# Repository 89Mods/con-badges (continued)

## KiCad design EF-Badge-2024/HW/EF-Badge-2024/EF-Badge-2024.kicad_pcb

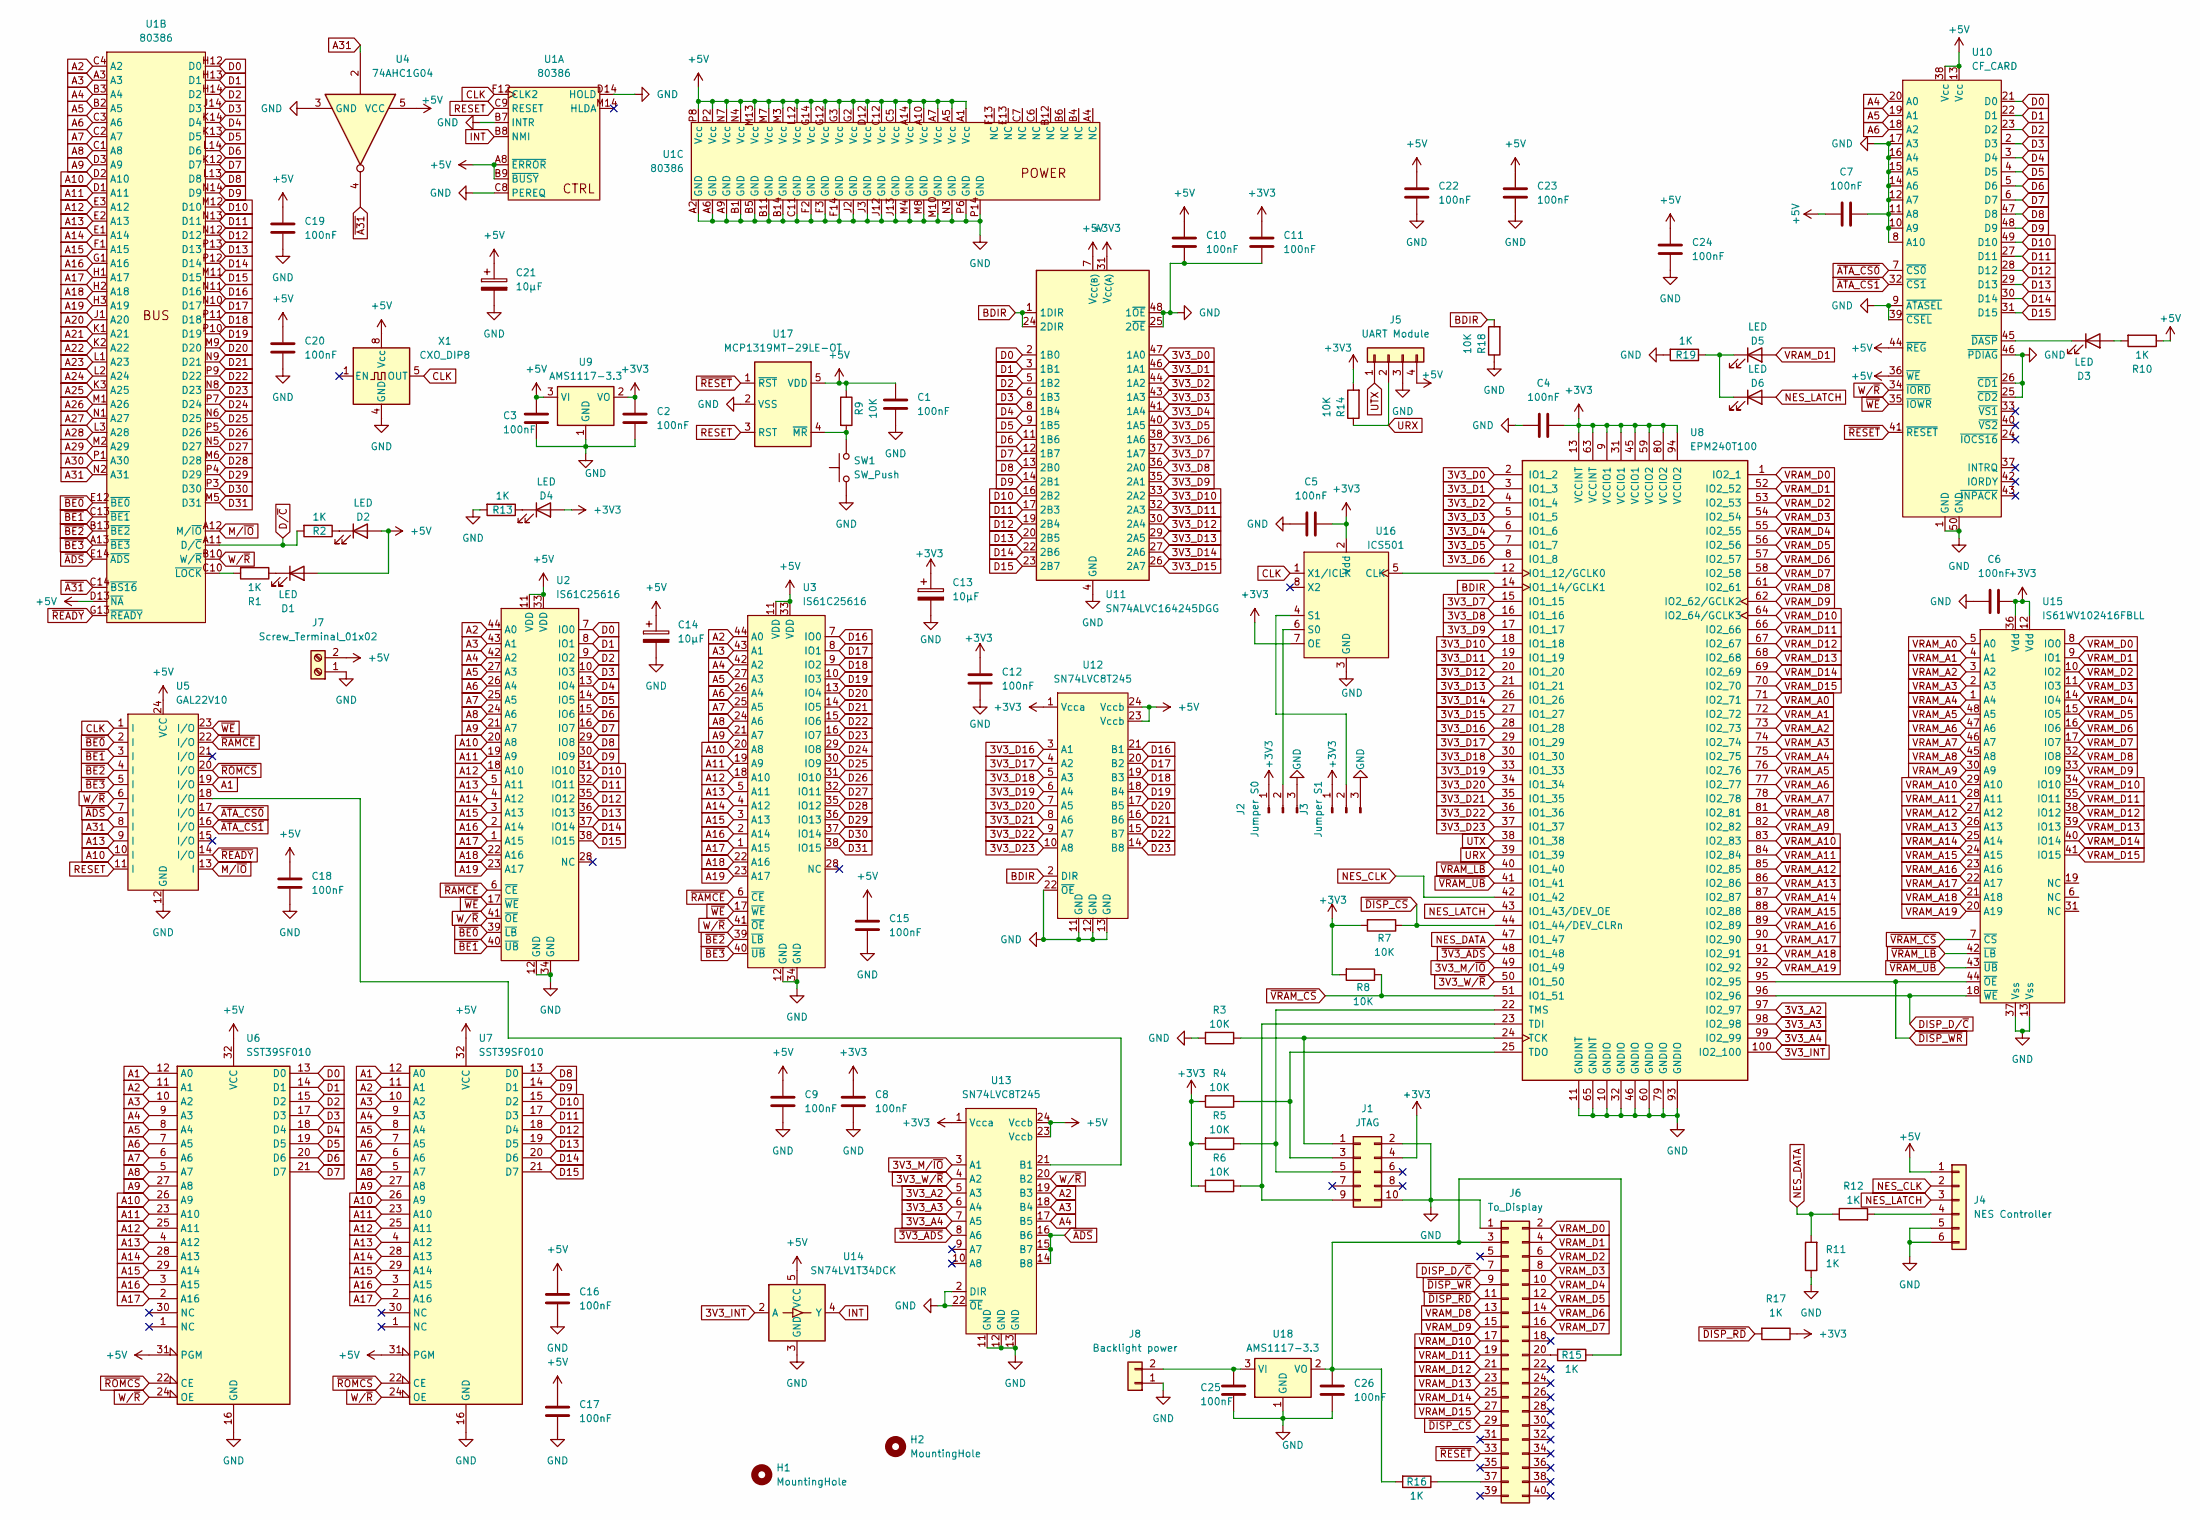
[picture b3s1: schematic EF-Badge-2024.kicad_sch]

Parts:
C1, C2, C3, C4, C5, C6, C7, C8, C9, C10, C11, C12, C15, C16, C17, C18, C19, C20, C22, C23, C24, C25, C26: 100nF; C_0805_2012Metric_Pad1.18x1.45mm_HandSolder
C13, C14, C21: 10µF; CP_Elec_3x5.4
D1, D2, D3, D4, D5, D6: LED; LED_1206_3216Metric_Pad1.42x1.75mm_HandSolder
H1, H2: MountingHole; MountingHole_3.2mm_M3_ISO7380
J1: JTAG; PinHeader_2x05_P2.54mm_Vertical
J2: Jumper S0; PinHeader_1x03_P2.54mm_Vertical
J3: Jumper S1; PinHeader_1x03_P2.54mm_Vertical
J4: NES Controller; PinSocket_1x06_P2.54mm_Vertical
J5: UART Module; PinHeader_1x04_P2.54mm_Vertical
J6: To_Display; PinHeader_2x20_P2.54mm_Vertical
J7: Screw_Terminal_01x02; TerminalBlock_bornier-2_P5.08mm
J8: Backlight power; PinHeader_1x02_P2.54mm_Vertical
R1, R2, R10, R11, R12, R13, R15, R16, R17, R19: 1K; R_1206_3216Metric_Pad1.30x1.75mm_HandSolder
R3, R4, R5, R6, R7, R8, R9, R14, R18: 10K; R_1206_3216Metric_Pad1.30x1.75mm_HandSolder
SW1: SW_Push; SW_PUSH_6mm
U1: 80386; Intel386DX
U2, U3: IS61C25616; TSOP-II-44_10.16x18.41mm_P0.8mm
U4: 74AHC1G04; SOIC-6
U5: GAL22V10; DIP-24_W7.62mm_Socket
U6, U7: SST39SF010; PLCC-32_THT-Socket
U8: EPM240T100; LQFP-100_14x14mm_P0.5mm
U9, U18: AMS1117-3.3; SOT-223-3_TabPin2
U10: CF_CARD; CF-Card_3M_N7E50-E516xx-30_fixed
U11: SN74ALVC164245DGG; TSSOP-48_6.1x12.5mm_P0.5mm
U12, U13: SN74LVC8T245; TSSOP-24_4.4x7.8mm_P0.65mm
U14: SN74LV1T34DCK; SOT-23-5
U15: IS61WV102416FBLL; TSOP-I-48_18.4x12mm_P0.5mm
U16: ICS501; SOIC-8_3.9x4.9mm_P1.27mm
U17: MCP1319MT-29LE-OT; SOT-23-5
X1: CXO_DIP8; Oscillator_DIP-8

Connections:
3V3_A2: U8.97 (IO2_97), U13.5 (A3)
3V3_A3: U8.98 (IO2_98), U13.6 (A4)
3V3_A4: U8.99 (IO2_99), U13.7 (A5)
3V3_D0: U8.2 (IO1_2), U11.47 (1A0)
3V3_D1: U8.3 (IO1_3), U11.46 (1A1)
3V3_D2: U8.4 (IO1_4), U11.44 (1A2)
3V3_D3: U8.5 (IO1_5), U11.43 (1A3)
3V3_D4: U8.6 (IO1_6), U11.41 (1A4)
3V3_D5: U8.7 (IO1_7), U11.40 (1A5)
3V3_D6: U8.8 (IO1_8), U11.38 (1A6)
3V3_D7: U8.15 (IO1_15), U11.37 (1A7)
3V3_D8: U8.16 (IO1_16), U11.36 (2A0)
3V3_D9: U8.17 (IO1_17), U11.35 (2A1)
3V3_D10: U8.18 (IO1_18), U11.33 (2A2)
3V3_D11: U8.19 (IO1_19), U11.32 (2A3)
3V3_D12: U8.20 (IO1_20), U11.30 (2A4)
3V3_D13: U8.21 (IO1_21), U11.29 (2A5)
3V3_D14: U8.26 (IO1_26), U11.27 (2A6)
3V3_D15: U8.27 (IO1_27), U11.26 (2A7)
3V3_D16: U8.28 (IO1_28), U12.3 (A1)
3V3_D17: U8.29 (IO1_29), U12.4 (A2)
3V3_D18: U8.30 (IO1_30), U12.5 (A3)
3V3_D19: U8.33 (IO1_33), U12.6 (A4)
3V3_D20: U8.34 (IO1_34), U12.7 (A5)
3V3_D21: U8.35 (IO1_35), U12.8 (A6)
3V3_D22: U8.36 (IO1_36), U12.9 (A7)
3V3_D23: U8.37 (IO1_37), U12.10 (A8)
3V3_INT: U8.100 (IO2_100), U14.2 (A)
3V3_M/~IO: U8.49 (IO1_49), U13.3 (A1)
3V3_W/~R: U8.50 (IO1_50), U13.4 (A2)
+3V3: C2.1, C4.2, C5.2, C6.2, C8.2, C11.2, C12.2, C13.1, D4.2 (A), J1.4, J2.1, J3.1, R4.2, R5.2, R6.2, R7.2, R8.2, R14.2, R17.1, U8.9 (VCCIO1), U8.13 (VCCINT), U8.31 (VCCIO1), U8.45 (VCCIO1), U8.59 (VCCIO2), U8.63 (VCCINT), U8.80 (VCCIO2), U8.94 (VCCIO2), U9.2 (VO), U11.31 (V_{CC(A)}), U11.42 (V_{CC(A)}), U12.1 (Vcca), U13.1 (Vcca), U15.12 (Vdd), U15.36 (Vdd), U16.2 (Vdd), U16.7 (OE)
+5V: C1.1, C3.1, C7.1, C9.2, C10.2, C14.1, C15.2, C16.2, C17.2, C18.2, C19.2, C20.2, C21.1, C22.2, C23.2, C24.2, D1.2 (A), D2.2 (A), J4.1, J5.4, J7.2, R9.1, R10.1, U1.A1 (Vcc), U1.A5 (Vcc), U1.A7 (Vcc), U1.A8 (~ERROR), U1.A10 (Vcc), U1.A14 (Vcc), U1.B9 (~BUSY), U1.C5 (Vcc), U1.C12 (Vcc), U1.D12 (Vcc), U1.D13 (~NA), U1.G2 (Vcc), U1.G3 (Vcc), U1.G12 (Vcc), U1.G14 (Vcc), U1.L12 (Vcc), U1.M3 (Vcc), U1.M7 (Vcc), U1.M13 (Vcc), U1.N4 (Vcc), U1.N7 (Vcc), U1.P2 (Vcc), U1.P8 (Vcc), U2.11 (VDD), U2.33 (VDD), U3.11 (VDD), U3.33 (VDD), U4.5 (VCC), U5.24 (VCC), U6.31 (PGM), U6.32 (VCC), U7.31 (PGM), U7.32 (VCC), U9.3 (VI), U10.13 (Vcc), U10.36 (~WE), U10.38 (Vcc), U10.44 (~REG), U11.7 (V_{CC(B)}), U11.18 (V_{CC(B)}), U12.23 (Vccb), U12.24 (Vccb), U13.23 (Vccb), U13.24 (Vccb), U14.5 (VCC), U17.5 (VDD), X1.8 (Vcc)
A1: U5.19 (I/O), U6.12 (A0), U7.12 (A0)
A2: U1.C4 (A2), U2.44 (A0), U3.44 (A0), U6.11 (A1), U7.11 (A1), U13.19 (B3)
A3: U1.A3, U2.43 (A1), U3.43 (A1), U6.10 (A2), U7.10 (A2), U13.18 (B4)
A4: U1.B3 (A4), U2.42 (A2), U3.42 (A2), U6.9 (A3), U7.9 (A3), U10.20 (A0), U13.17 (B5)
A5: U1.B2 (A5), U2.27 (A3), U3.27 (A3), U6.8 (A4), U7.8 (A4), U10.19 (A1)
A6: U1.C3 (A6), U2.26 (A4), U3.26 (A4), U6.7 (A5), U7.7 (A5), U10.18 (A2)
A7: U1.C2 (A7), U2.25 (A5), U3.25 (A5), U6.6 (A6), U7.6 (A6)
A8: U1.C1 (A8), U2.24 (A6), U3.24 (A6), U6.5 (A7), U7.5 (A7)
A9: U1.D3 (A9), U2.21 (A7), U3.21 (A7), U6.27 (A8), U7.27 (A8)
A10: U1.D2 (A10), U2.20 (A8), U3.20 (A8), U5.10 (I), U6.26 (A9), U7.26 (A9)
A11: U1.D1 (A11), U2.19 (A9), U3.19 (A9), U6.23 (A10), U7.23 (A10)
A12: U1.E3 (A12), U2.18 (A10), U3.18 (A10), U6.25 (A11), U7.25 (A11)
A13: U1.E2 (A13), U2.5 (A11), U3.5 (A11), U5.9 (I), U6.4 (A12), U7.4 (A12)
A14: U1.E1 (A14), U2.4 (A12), U3.4 (A12), U6.28 (A13), U7.28 (A13)
A15: U1.F1 (A15), U2.3 (A13), U3.3 (A13), U6.29 (A14), U7.29 (A14)
A16: U1.G1 (A16), U2.2 (A14), U3.2 (A14), U6.3 (A15), U7.3 (A15)
A17: U1.H1 (A17), U2.1 (A15), U3.1 (A15), U6.2 (A16), U7.2 (A16)
A18: U1.H2 (A18), U2.22 (A16), U3.22 (A16)
A19: U1.H3 (A19), U2.23 (A17), U3.23 (A17)
A20: U1.J1 (A20)
A21: U1.K1 (A21)
A22: U1.K2 (A22)
A23: U1.L1 (A23)
A24: U1.L2 (A24)
A25: U1.K3 (A25)
A26: U1.M1 (A26)
A27: U1.N1 (A27)
A28: U1.L3 (A28)
A29: U1.M2 (A29)
A30: U1.P1 (A30)
A31: U1.N2 (A31), U4.2, U5.8 (I)
BDIR: R18.2, U8.14 (IO1_14/GCLK1), U11.1 (1DIR), U11.24 (2DIR), U12.2 (DIR)
CLK: U1.F12 (CLK2), U5.1 (I), U16.1 (X1/ICLK), X1.5 (OUT)
D0: U1.H12 (D0), U2.7 (IO0), U6.13 (D0), U10.21 (D0), U11.2 (1B0)
D1: U1.H13 (D1), U2.8 (IO1), U6.14 (D1), U10.22 (D1), U11.3 (1B1)
D2: U1.H14 (D2), U2.9 (IO2), U6.15 (D2), U10.23 (D2), U11.5 (1B2)
D3: U1.J14 (D3), U2.10 (IO3), U6.17 (D3), U10.2 (D3), U11.6 (1B3)
D4: U1.K14 (D4), U2.13 (IO4), U6.18 (D4), U10.3 (D4), U11.8 (1B4)
D5: U1.K13 (D5), U2.14 (IO5), U6.19 (D5), U10.4 (D5), U11.9 (1B5)
D6: U1.L14 (D6), U2.15 (IO6), U6.20 (D6), U10.5 (D6), U11.11 (1B6)
D7: U1.K12 (D7), U2.16 (IO7), U6.21 (D7), U10.6 (D7), U11.12 (1B7)
D8: U1.L13 (D8), U2.29 (IO8), U7.13 (D0), U10.47 (D8), U11.13 (2B0)
D9: U1.N14 (D9), U2.30 (IO9), U7.14 (D1), U10.48 (D9), U11.14 (2B1)
D10: U1.M12 (D10), U2.31 (IO10), U7.15 (D2), U10.49 (D10), U11.16 (2B2)
D11: U1.N13 (D11), U2.32 (IO11), U7.17 (D3), U10.27 (D11), U11.17 (2B3)
D12: U1.N12 (D12), U2.35 (IO12), U7.18 (D4), U10.28 (D12), U11.19 (2B4)
D13: U1.P13 (D13), U2.36 (IO13), U7.19 (D5), U10.29 (D13), U11.20 (2B5)
D14: U1.P12 (D14), U2.37 (IO14), U7.20 (D6), U10.30 (D14), U11.22 (2B6)
D15: U1.M11 (D15), U2.38 (IO15), U7.21 (D7), U10.31 (D15), U11.23 (2B7)
D16: U1.N11 (D16), U3.7 (IO0), U12.21 (B1)
D17: U1.N10 (D17), U3.8 (IO1), U12.20 (B2)
D18: U1.P11 (D18), U3.9 (IO2), U12.19 (B3)
D19: U1.P10 (D19), U3.10 (IO3), U12.18 (B4)
D20: U1.M9 (D20), U3.13 (IO4), U12.17 (B5)
D21: U1.N9 (D21), U3.14 (IO5), U12.16 (B6)
D22: U1.P9 (D22), U3.15 (IO6), U12.15 (B7)
D23: U1.N8 (D23), U3.16 (IO7), U12.14 (B8)
D24: U1.P7 (D24), U3.29 (IO8)
D25: U1.N6 (D25), U3.30 (IO9)
D26: U1.P5 (D26), U3.31 (IO10)
D27: U1.N5 (D27), U3.32 (IO11)
D28: U1.M6 (D28), U3.35 (IO12)
D29: U1.P4 (D29), U3.36 (IO13)
D30: U1.P3 (D30), U3.37 (IO14)
D31: U1.M5 (D31), U3.38 (IO15)
DISP_D/~C: J6.7, U8.96 (IO2_96), U15.18 (~WE)
D/~C: R2.2, U1.A11 (D/~C)
GND: C1.2, C2.2, C3.2, C4.1, C5.1, C6.1, C7.2, C8.1, C9.1, C10.1, C11.1, C12.1, C13.2, C14.2, C15.1, C16.1, C17.1, C18.1, C19.1, C20.1, C21.2, C22.1, C23.1, C24.1, C25.2, C26.2, J1.2, J1.10, J2.3, J3.3, J4.5, J4.6, J5.3, J6.1, J7.1, J8.1, R3.2, R11.1, R13.2, R18.1, R19.2, SW1.1, U1.A2 (GND), U1.A6 (GND), U1.A9 (GND), U1.B1 (GND), U1.B5 (GND), U1.B7 (INTR), U1.B11 (GND), U1.B14 (GND), U1.C8 (PEREQ), U1.C11 (GND), U1.D14 (HOLD), U1.F2 (GND), U1.F3 (GND), U1.F14 (GND), U1.J2 (GND), U1.J3 (GND), U1.J12 (GND), U1.J13 (GND), U1.M4 (GND), U1.M8 (GND), U1.M10 (GND), U1.N3 (GND), U1.P6 (GND), U1.P14 (GND), U2.12 (GND), U2.34 (GND), U3.12 (GND), U3.34 (GND), U4.3 (GND), U5.12 (GND), U6.16 (GND), U7.16 (GND), U8.10 (GNDIO), U8.11 (GNDINT), U8.32 (GNDIO), U8.46 (GNDIO), U8.60 (GNDIO), U8.65 (GNDINT), U8.79 (GNDIO), U8.93 (GNDIO), U9.1 (GND), U10.1 (GND), U10.8 (A10), U10.9 (~ATASEL), U10.10 (A9), U10.11 (A8), U10.12 (A7), U10.14 (A6), U10.15 (A5), U10.16 (A4), U10.17 (A3), U10.25 (~CD2), U10.26 (~CD1), U10.39 (~CSEL), U10.46 (~PDIAG), U10.50 (GND), U11.4 (GND), U11.10 (GND), U11.15 (GND), U11.21 (GND), U11.25 (2~OE), U11.28 (GND), U11.34 (GND), U11.39 (GND), U11.45 (GND), U11.48 (1~OE), U12.11 (GND), U12.12 (GND), U12.13 (GND), U12.22 (~OE), U13.2 (DIR), U13.11 (GND), U13.12 (GND), U13.13 (GND), U13.22 (~OE), U14.3 (GND), U15.13 (Vss), U15.37 (Vss), U16.3 (GND), U17.2 (VSS), U18.1 (GND), X1.4 (GND)
INT: U1.B8 (NMI), U14.4 (Y)
M/~IO: U1.A12 (M/~IO), U5.13 (I)
NES_CLK: J4.2, U8.42 (IO1_42)
NES_DATA: R11.2, R12.1, U8.47 (IO1_47)
NES_LATCH: D6.2 (A), J4.3, U8.43 (IO1_43/DEV_OE)
unnamed: D1.1 (K), R1.1
unnamed: D2.1 (K), R2.1
unnamed: D3.2 (A), R10.2
unnamed: D3.1 (K), U10.45 (~DASP)
unnamed: D4.1 (K), R13.1
unnamed: D5.1 (K), D6.1 (K), R19.1
unnamed: J1.1, R3.1, U8.24 (TCK)
unnamed: J1.3, R4.1, U8.25 (TDO)
unnamed: J1.5, R5.1, U8.22 (TMS)
unnamed: J1.9, R6.1, U8.23 (TDI)
unnamed: J2.2, U16.6 (S0)
unnamed: J3.2, U16.4 (S1)
unnamed: J4.4, R12.2
unnamed: C26.1, J6.3, R15.1, R16.2, U18.2 (VO)
unnamed: J6.20, R15.2
unnamed: J6.37, R16.1
unnamed: C25.1, J8.2, U18.3 (VI)
unnamed: R1.2, U1.C10 (~LOCK)
unnamed: U5.18 (I/O), U13.21 (B1)
unnamed: U8.12 (IO1_12/GCLK0), U16.5 (CLK)
unnamed: R9.2, SW1.2, U17.4 (~MR)
RESET: U1.C9 (RESET), U5.11 (I), U17.3 (RST)
URX: J5.2, R14.1, U8.39 (IO1_39)
UTX: J5.1, U8.38 (IO1_38)
VRAM_A0: U8.71 (IO2_71), U15.5 (A0)
VRAM_A1: U8.72 (IO2_72), U15.4 (A1)
VRAM_A2: U8.73 (IO2_73), U15.3 (A2)
VRAM_A3: U8.74 (IO2_74), U15.2 (A3)
VRAM_A4: U8.75 (IO2_75), U15.1 (A4)
VRAM_A5: U8.76 (IO2_76), U15.48 (A5)
VRAM_A6: U8.77 (IO2_77), U15.47 (A6)
VRAM_A7: U8.78 (IO2_78), U15.46 (A7)
VRAM_A8: U8.81 (IO2_81), U15.45 (A8)
VRAM_A9: U8.82 (IO2_82), U15.30 (A9)
VRAM_A10: U8.83 (IO2_83), U15.29 (A10)
VRAM_A11: U8.84 (IO2_84), U15.28 (A11)
VRAM_A12: U8.85 (IO2_85), U15.27 (A12)
VRAM_A13: U8.86 (IO2_86), U15.26 (A13)
VRAM_A14: U8.87 (IO2_87), U15.25 (A14)
VRAM_A15: U8.88 (IO2_88), U15.24 (A15)
VRAM_A16: U8.89 (IO2_89), U15.23 (A16)
VRAM_A17: U8.90 (IO2_90), U15.22 (A17)
VRAM_A18: U8.91 (IO2_91), U15.21 (A18)
VRAM_A19: U8.92 (IO2_92), U15.20 (A19)
VRAM_D0: J6.2, U8.1 (IO2_1), U15.8 (IO0)
VRAM_D1: D5.2 (A), J6.4, U8.52 (IO2_52), U15.9 (IO1)
VRAM_D2: J6.6, U8.53 (IO2_53), U15.10 (IO2)
VRAM_D3: J6.8, U8.54 (IO2_54), U15.11 (IO3)
VRAM_D4: J6.10, U8.55 (IO2_55), U15.14 (IO4)
VRAM_D5: J6.12, U8.56 (IO2_56), U15.15 (IO5)
VRAM_D6: J6.14, U8.57 (IO2_57), U15.16 (IO6)
VRAM_D7: J6.16, U8.58 (IO2_58), U15.17 (IO7)
VRAM_D8: J6.13, U8.61 (IO2_61), U15.32 (IO8)
VRAM_D9: J6.15, U8.62 (IO2_62/GCLK2), U15.33 (IO9)
VRAM_D10: J6.17, U8.64 (IO2_64/GCLK3), U15.34 (IO10)
VRAM_D11: J6.19, U8.66 (IO2_66), U15.35 (IO11)
VRAM_D12: J6.21, U8.67 (IO2_67), U15.38 (IO12)
VRAM_D13: J6.23, U8.68 (IO2_68), U15.39 (IO13)
VRAM_D14: J6.25, U8.69 (IO2_69), U15.40 (IO14)
VRAM_D15: J6.27, U8.70 (IO2_70), U15.41 (IO15)
W/~R: U1.B10 (W/~R), U2.41 (~OE), U3.41 (~OE), U5.6 (I), U6.24 (OE), U7.24 (OE), U10.34 (~IORD), U13.20 (B2)
~3V3_ADS: U8.48 (IO1_48), U13.8 (A6)
~A31: U1.C14 (~BS16), U4.4
~ADS: U1.E14 (~ADS), U5.7 (I), U13.14 (B8), U13.15 (B7), U13.16 (B6)
~ATA_CS0: U5.17 (I/O), U10.7 (~CS0)
~ATA_CS1: U5.16 (I/O), U10.32 (~CS1)
~BE0: U1.E12 (~BE0), U2.39 (~LB), U5.2 (I)
~BE1: U1.C13 (~BE1), U2.40 (~UB), U5.3 (I)
~BE2: U1.B13 (~BE2), U3.39 (~LB), U5.4 (I)
~BE3: U1.A13 (~BE3), U3.40 (~UB), U5.5 (I)
~DISP_CS: J6.29, R7.1, U8.44 (IO1_44/DEV_CLRn)
~DISP_RD: J6.11, R17.2
~DISP_WR: J6.9, U8.95 (IO2_95), U15.44 (~OE)
~RAMCE: U2.6 (~CE), U3.6 (~CE), U5.22 (I/O)
~READY: U1.G13 (~READY), U5.14 (I/O)
~RESET: J6.33, U10.41 (~RESET), U17.1 (~RST)
~ROMCS: U5.20 (I/O), U6.22 (CE), U7.22 (CE)
~VRAM_CS: R8.1, U8.51 (IO1_51), U15.7 (~CS)
~VRAM_LB: U8.40 (IO1_40), U15.42 (~LB)
~VRAM_UB: U8.41 (IO1_41), U15.43 (~UB)
~WE: U2.17 (~WE), U3.17 (~WE), U5.23 (I/O), U10.35 (~IOWR)

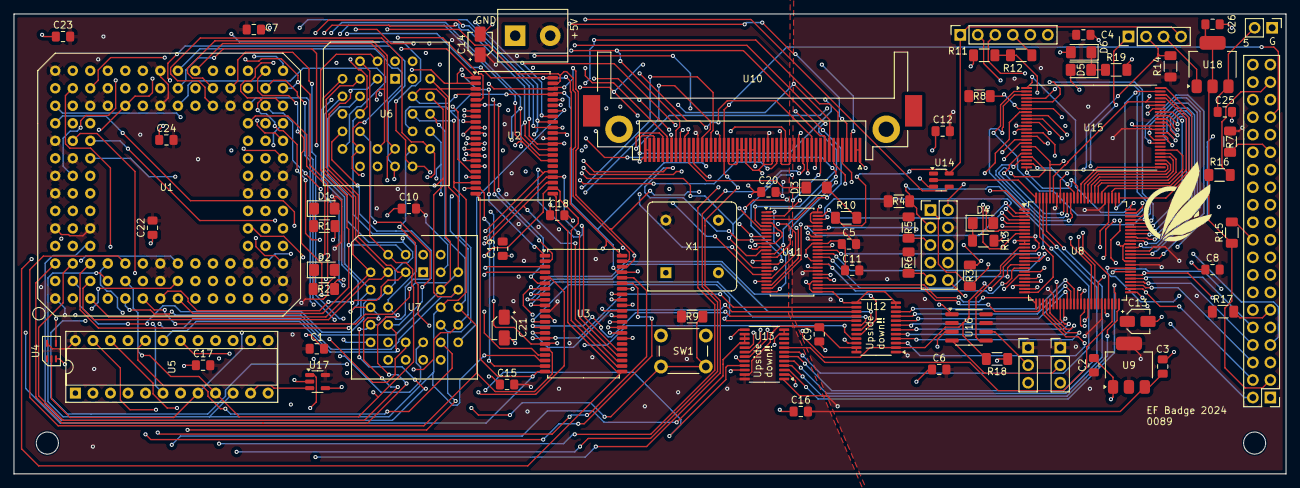
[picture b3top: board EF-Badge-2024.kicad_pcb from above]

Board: 4 copper layers, 184.4 x 66.7 mm, 81 parts (0 on the bottom side), 175 nets.

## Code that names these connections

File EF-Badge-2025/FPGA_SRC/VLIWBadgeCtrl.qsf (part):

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set_location_assignment PIN_59 -to AD[2]
set_location_assignment PIN_55 -to AD[1]
set_location_assignment PIN_54 -to AD[0]
set_location_assignment PIN_8 -to CPU_INTERRUPT
set_location_assignment PIN_23 -to DAC_clk
set_location_assignment PIN_26 -to DAC_csb
set_location_assignment PIN_24 -to DAC_dat
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set_location_assignment PIN_114 -to DISP_RDb
set_location_assignment PIN_116 -to DISP_RESETb
set_location_assignment PIN_112 -to DISP_WRb
set_location_assignment PIN_19 -to LED_CKI
set_location_assignment PIN_21 -to LED_SDI
set_location_assignment PIN_46 -to LE_HI
set_location_assignment PIN_44 -to LE_LO
set_location_assignment PIN_42 -to OEb
set_location_assignment PIN_6 -to RXD
set_location_assignment PIN_7 -to TXD
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set_location_assignment PIN_4 -to cpu_resetb
set_location_assignment PIN_88 -to inclk
set_location_assignment PIN_113 -to porb
set_location_assignment PIN_39 -to xclk
set_instance_assignment -name IO_STANDARD "3.3-V LVTTL" -to VRAM_A[19]
set_instance_assignment -name IO_STANDARD "3.3-V LVTTL" -to VRAM_A[18]
set_instance_assignment -name IO_STANDARD "3.3-V LVTTL" -to VRAM_WEb
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
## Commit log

2024-09-29 Initial commit, EF 2024 badge
2025-08-08 Add CPLD quartus project
2025-09-15 2025 Badge
